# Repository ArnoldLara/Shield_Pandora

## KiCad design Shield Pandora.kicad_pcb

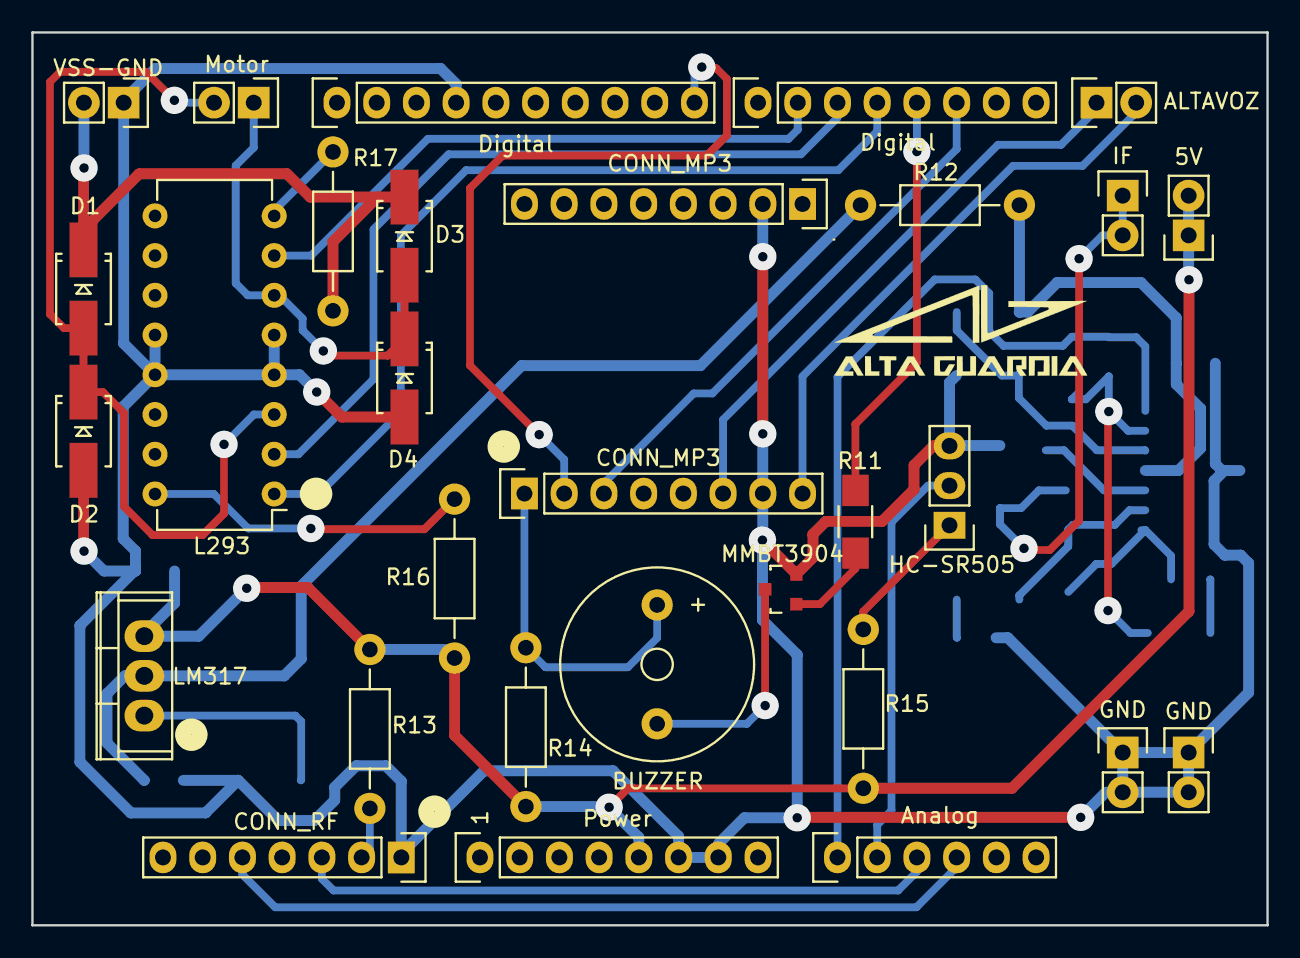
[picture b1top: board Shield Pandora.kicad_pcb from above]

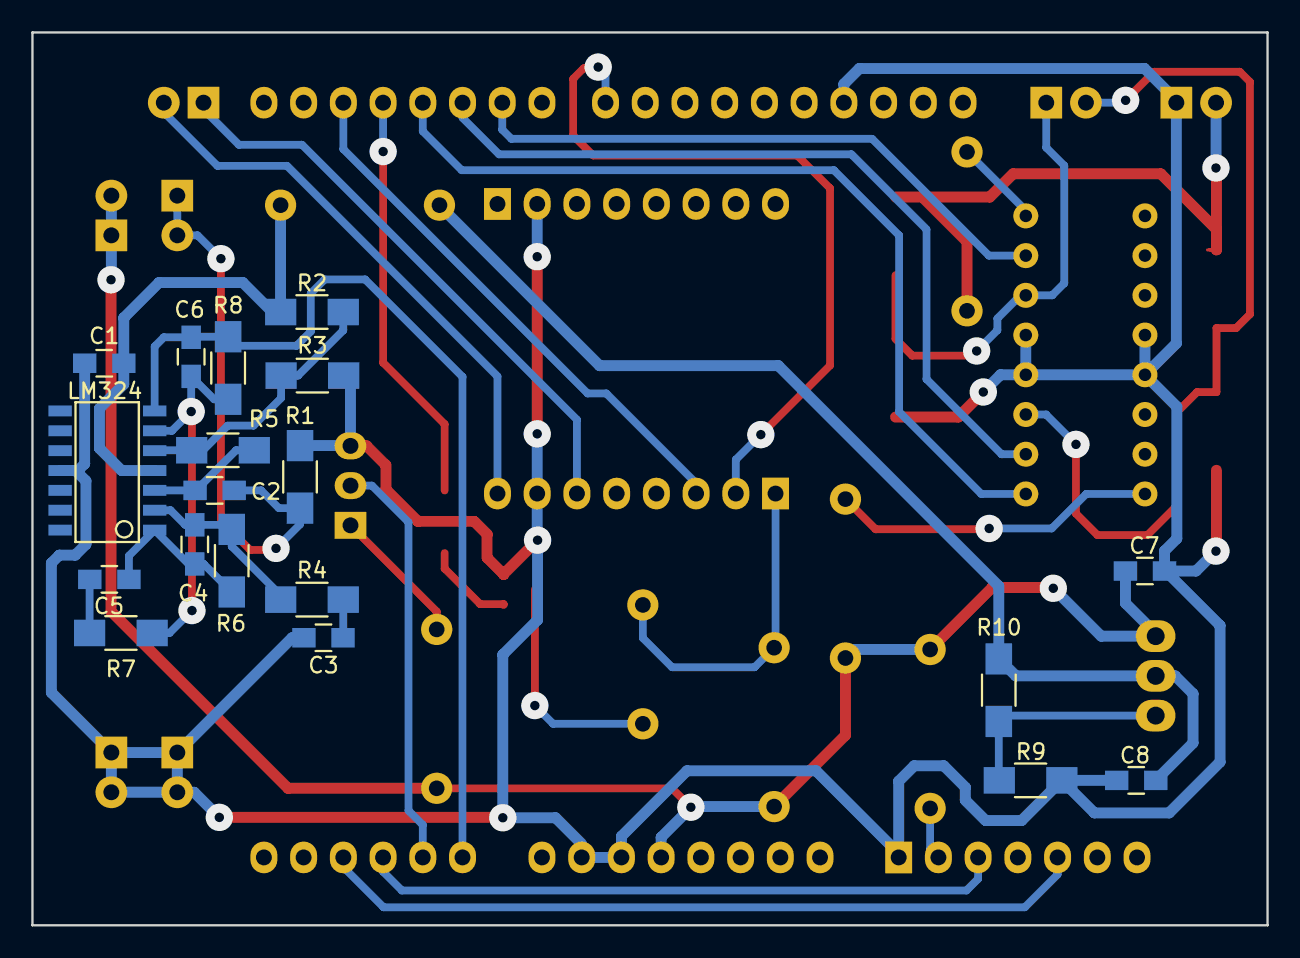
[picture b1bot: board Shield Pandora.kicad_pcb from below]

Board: 2 copper layers, 79.0 x 57.1 mm, 49 parts (19 on the bottom side), 35 nets.

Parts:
C1, C7: 0.1uF; C_0805_HandSoldering
C2, C3, C4, C5, C6: 4.7uF; C_0805_HandSoldering
C8: 1uF; C_0805_HandSoldering
D1, D2, D3, D4: D; SMA_Handsoldering
P1: Power; Socket_Strip_Arduino_1x08
P2: Analog; Socket_Strip_Arduino_1x06
P3: Digital; Socket_Strip_Arduino_1x10
P4: Digital; Socket_Strip_Arduino_1x08
P5: VSS-GND; Pin_Header_Straight_1x02
P6: Motor; Pin_Header_Straight_1x02
P9: 5V; Pin_Header_Straight_1x02
P10: IF; Pin_Header_Straight_1x02
P11, P12: GND; Pin_Header_Straight_1x02
P13: CONN_RF; Pin_Header_Straight_1x07
P14: HC-SR505; Pin_Header_Straight_1x03
P15, P16: CONN_MP3; Pin_Header_Straight_1x08
Q1: MMBT3904; SOT-23
R1: 12k; R_1206_HandSoldering
R2, R3, R5: 330k; R_1206_HandSoldering
R4: 10k; R_1206_HandSoldering
R6, R8: 1M; R_1206_HandSoldering
R7: 8.2k; R_1206_HandSoldering
R9: 2.2k; R_1206_HandSoldering
R10, R11: 1k; R_1206_HandSoldering
R12, R13, R14, R15, R16, R17: 0.1; Resistor_Horizontal_RM10mm
SP1: BUZZER; Buzzer_12x9.5RM7.6
SP2: ALTAVOZ; Pin_Header_Straight_1x02
U1: LM324
U2: LM317; TO-220
U3: L293; DIP-16_W7.62mm

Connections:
+5V: C7.1, P1.5, P9.1, P9.2, R13.2, R14.2, R15.2, R16.1, U2.3
+9V: D1.1, D3.1, P5.2, R17.1
/AN_OUT: C6.2, P2.1, R8.1, U1.7
/Amplificador_HB100/+4V: C1.1, R2.2, R12.1, U1.4
/BZR: P4.5, R11.1
/DF_Player/+5V: P15.1, R14.1, SP1.1
/DF_Player/SPK1: P15.6, SP2.1
/DF_Player/SPK2: P15.8, SP2.2
/ENA: P4.4, U3.1
/IA1: P4.3, U3.2
/IA2: P4.2, U3.7
/IF: C2.1, P10.1, P10.2, R1.2
/MOTOR_1: D1.2, D2.1, P6.2, U3.3
/MOTOR_2: D3.2, D4.1, P6.1, U3.6
/MP3_RX: P3.10, P15.2
/MP3_TX: P4.6, P15.3
/PIR: P2.2, P14.2
/TCL_A: P2.4, P13.5
/TCL_B: P2.3, P13.3
GND: C1.2, C3.2, C7.2, C8.2, D2.2, D4.2, P1.6, P1.7, P3.4, P5.1, P11.1, P11.2, P12.1, P12.2, P13.1, P14.3, P15.7, P16.2, Q1.2, R1.1, R3.1, R9.2, U1.11, U3.4, U3.5, U3.12, U3.13
unnamed: C2.2, R5.1, U1.3
unnamed: C3.1, R4.1
unnamed: C4.1, R4.2, R6.2, U1.2
unnamed: C4.2, C5.1, R6.1, U1.1
unnamed: C5.2, R7.2
unnamed: C6.1, R7.1, R8.2, U1.6
unnamed: P13.2, R13.1
unnamed: P14.1, R15.1
unnamed: Q1.1, R11.2
unnamed: Q1.3, SP1.2
unnamed: R2.1, R3.2, R5.2, U1.5
unnamed: R9.1, R10.2, U2.1
unnamed: R16.2, U3.16
unnamed: R17.2, U3.8
VPP: C8.1, R10.1, R12.2, U2.2

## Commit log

2017-03-02 Se agrego proyecto
